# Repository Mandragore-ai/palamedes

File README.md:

# Alea Palamedis — dés connectés pour Mandragore

**[Mandragore.ai](https://mandragore.ai/) · [Maitresinh@500nuancesdegeek.fr](mailto:Maitresinh@500nuancesdegeek.fr)**

**Licences :** firmware hardware et logiciels sous **AGPL-3.0**, logo et documentation sous **CC BY-SA 4.0**. Citation et partage à l'identique obligatoires ; licence commerciale sur demande pour qui ne veut pas publier ses modifications. Détails : [LICENCES.md](LICENCES.md).

**Mandragore.ai · 23 novembre 2026 · prototype : conçu et simulé, pas encore fabriqué**

Selon la légende, Palamède a inventé les dés pendant le siège de Troie, puis les a consacrés à Tyché, déesse du hasard. *Alea Palamedis*, ce sont ses dés, avec du Bluetooth.

Chaque dé connaît la face sur laquelle il s'arrête et l'annonce par Bluetooth au **Mentor** (aide au MJ pendant la partie de jeu de rôle) et au **Sage en direct** (jeux de plateau). Le Mentor reçoit le jet comme un fait, sans devoir le deviner dans la parole, et le relie à l'action déclenchée et à la fiche du personnage. Le dé peut aussi signaler sa valeur à une tablette ou à un plateau à l'encre conductrice par des pastilles capacitives invisibles, cachées sous la peinture.

## Principe

- **Pas de circuit souple ni de moulage délicat** : un petit cœur rond (Ø16 mm) est noyé dans la résine, à l'intérieur d'une coque imprimée en deux parties qui sert de moule. Le dé final est plein et équilibré.
- **Électronique** : module Bluetooth Fanstel BC832 (nRF52832), accéléromètre LIS2DH12, pile bouton rechargeable LIR1254, recharge sans fil.
- **Recharge** : une boîte recharge les 7 dés d'un set. Une bobine gravée dans le circuit imprimé se trouve sous chaque logement ; chaque emplacement détecte le dé posé et s'arrête seul.
- **Premier dé : D20.** Le D4 est un D8 numéroté deux fois de 1 à 4. Les coques D6, D8, D10 et D12 restent à dessiner.

## Points forts

- Cout minimisé
- Consommation électrique minimisée (autonomie accrue)
- Taille réduite (similaire à des dés normaux)
- Coque interchangeable (perrmet de changer de type de dé avec le même coeur)
- Présence, localisation et identité du dé (et résultat) transmis à un écran capacitif

## Contenu du dépôt

| Dossier | Contenu | État |
|---|---|---|
| [`materiel/coeur`](materiel/coeur) | cœur du dé v0.3 : paquet de commande JLCPCB (Gerbers, nomenclature, placement), projet KiCad | contrôle de conception sans erreur |
| [`materiel/chargeur`](materiel/chargeur) | carte émettrice de la boîte v0.1 : paquet JLCPCB, projet KiCad | contrôle de conception sans erreur |
| [`coques`](coques) | coque D20 en deux parties (STL), patron A4 des pastilles, notice de montage | à imprimer |
| [`boite`](boite) | boîte-chargeur 7 dés (STL) et sa notice | à imprimer |
| [`firmware`](firmware) | firmware du dé (nRF52) et du chargeur (CH32V203), binaires, variante de carte | compilé, pas encore essayé sur le matériel |
| [`logiciel`](logiciel) | client Web Bluetooth (TypeScript), journal des jets pour le Mentor, module Tabletop Kit, note d'intégration Mandragore | types vérifiés |
| [`simulations`](simulations) | pastilles capacitives (BEM), recharge sans fil (SPICE, Monte-Carlo), résultats | voir ci-dessous |
| [`scripts`](scripts) | génération des circuits (KiCad / pcbnew), routeur, coques et boîte (trimesh) | — |

## Ce qui a été simulé

- **Pastilles capacitives** (simulation électrostatique) : avec 4 groupes de pastilles dispersés sur les faces, le signal garde 76 à 84 % de celui d'une pastille indépendante par face. Sur une tablette, il atteint environ 36 à 46 % du signal d'un doigt.
- **Recharge sans fil** : la tension reçue dans le dé reste entre 5,0 et 5,7 V pour un écart de 1,5 à 2,5 mm et un décentrage jusqu'à 1,5 mm, tolérances des composants comprises (Monte-Carlo). Pile pleine, le dé court-circuite sa bobine pour ne rien chauffer.

## À valider sur le premier prototype

1. Mesurer la tension de recharge reçue dans le dé et le seuil de détection du chargeur.
2. Faire une mise à jour Bluetooth complète **avant** de couler la résine.
3. Vérifier l'équité du dé : 500 lancers et un test du χ².

Vous poursuivez ce travail ? Envoyez-nous vos mesures et vos améliorations, ou ouvrez une issue / pull request.

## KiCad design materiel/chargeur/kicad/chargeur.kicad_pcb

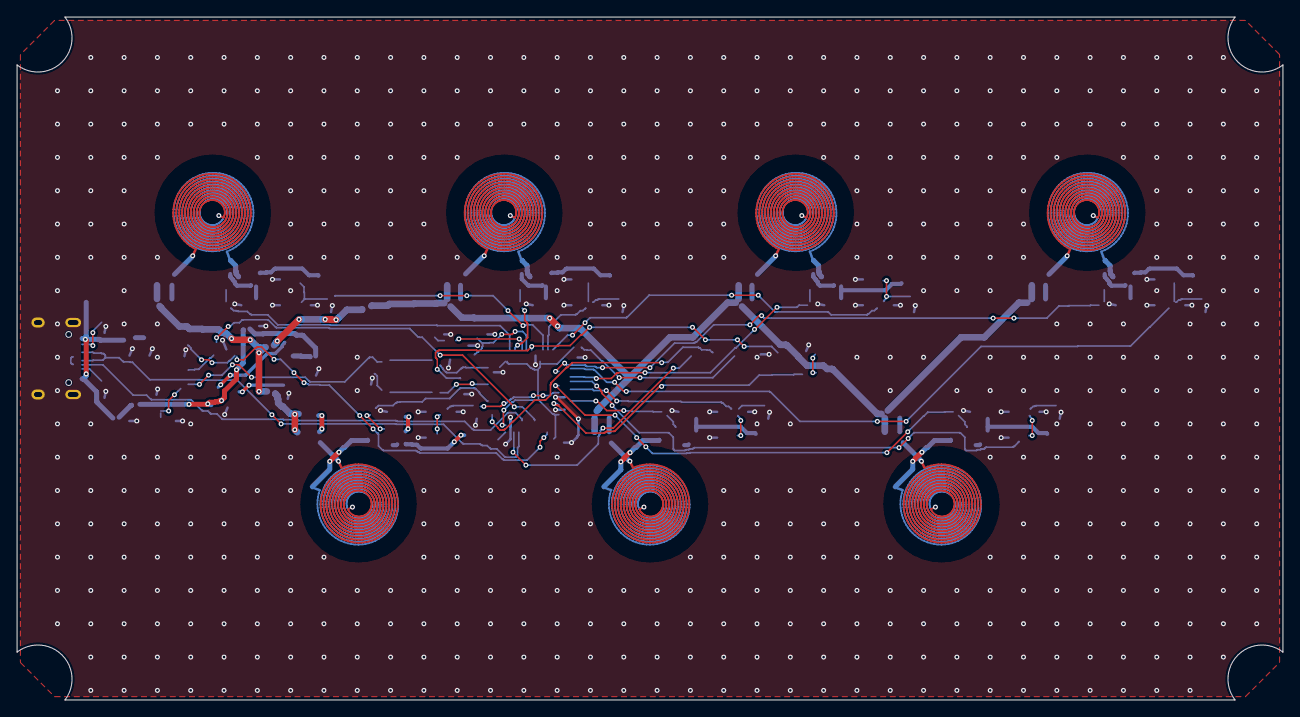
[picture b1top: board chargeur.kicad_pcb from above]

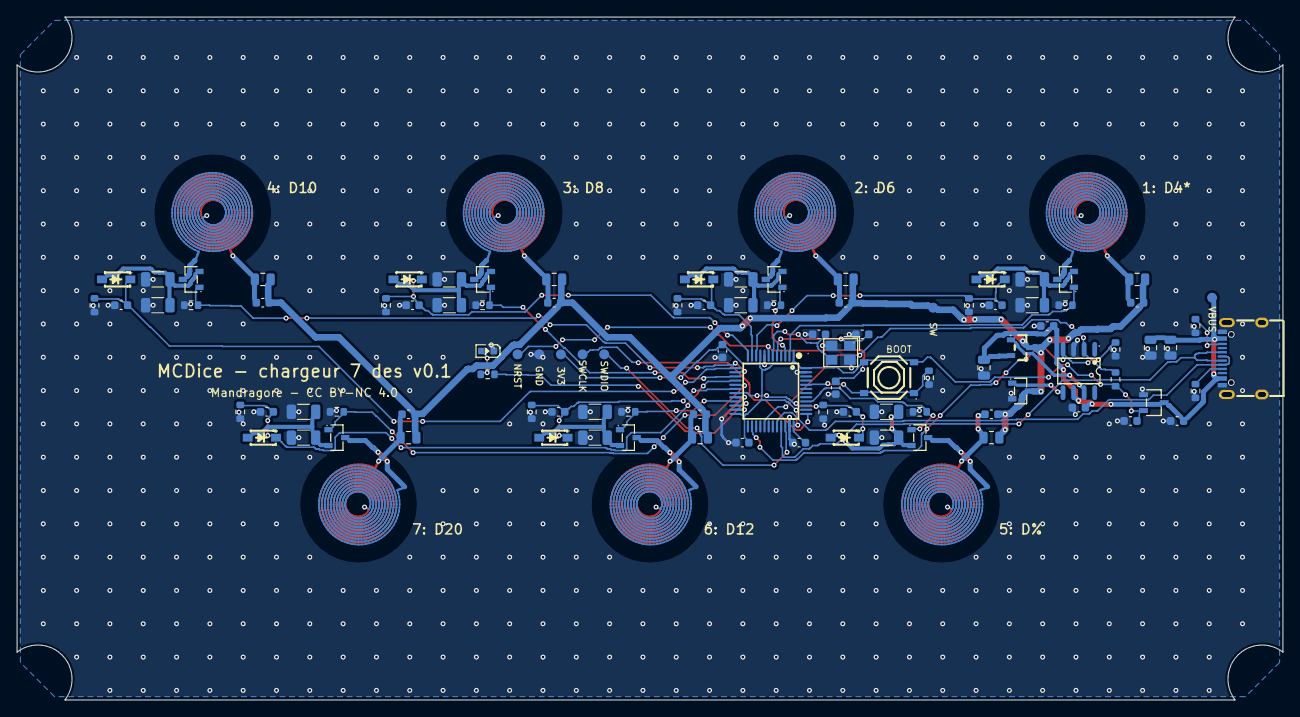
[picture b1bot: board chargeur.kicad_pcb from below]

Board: 2 copper layers, 152.0 x 82.0 mm, 98 parts (98 on the bottom side), 48 nets.

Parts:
C1, C2, C6: 22uF; C_0805_2012Metric
C3, C4, C5: 1uF; C_0603_1608Metric
C7, C10, C11, C12, C14, C41, C42, C43, C44, C45, C46, C47: 100nF; C_0603_1608Metric
C8, C9: 20pF; C_0603_1608Metric
C21, C22, C23, C24, C25, C26, C27: 10nF C0G; C_0805_2012Metric
C31, C32, C33, C34, C35, C36, C37: 2.2nF C0G; C_0603_1608Metric
D1: LED verte; LED0603-RD
D11, D12, D13, D14, D15, D16, D17: B5819W; SOD-123_L2.7-W1.6-LS3.7-RD-1
J1: USB-C 16P; USB-C-SMD_TYPE-C-16PIN-2MD-073
Q1: AO3401A; SOT-23_L2.9-W1.3-P1.90-LS2.4-BR
Q2, Q11, Q12, Q13, Q14, Q15, Q16, Q17: AO3400A; SOT-23-3_L2.9-W1.3-P1.90-LS2.4-BR
R1, R2: 5.1k; R_0603_1608Metric
R3, R4, R5: 10k; R_0603_1608Metric
R6: 1k; R_0603_1608Metric
R11, R12, R13, R14, R15, R16, R17, R41, R42, R43, R44, R45, R46, R47: 100k; R_0603_1608Metric
R21, R22, R23, R24, R25, R26, R27, R31, R32, R33, R34, R35, R36, R37: 2.2R; R_1206_3216Metric
SW1: BOOT; SW-SMD_4P-L5.1-W5.1-P3.70-LS6.5-TL_H1.5
TP1: SWDIO; TP_SWDIO
TP2: SWCLK; TP_SWCLK
TP3: 3V3; TP_3V3
TP4: GND; TP_GND
TP5: SW; TP_SW
TP6: VBUS; TP_VBUS
TP7: NRST; TP_NRST
U1: XC6206P332MR; SOT-23-3_L2.9-W1.6-P1.90-LS2.8-BR
U2: UCC27524ADR; SOIC-8_L4.9-W3.9-P1.27-LS6.0-BL
U3: CH32V203C8T6; LQFP-48_L7.0-W7.0-P0.50-LS9.0-BL
Y1: 8MHz; CRYSTAL-SMD_4P-L3.2-W2.5-BL

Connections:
3V3: C4.1, C10.1, C11.1, C12.1, R3.2, SW1.3, SW1.4, TP3.1, U1.2, U3.1, U3.9, U3.24, U3.36, U3.48
BOOT0: R5.1, SW1.1, SW1.2, U3.44
CC1: J1.A5, R1.1
CC2: J1.B5, R2.1
COIL1: C21.2, C31.2, Q11.3
COIL2: C22.2, C32.2, Q12.3
COIL3: C23.2, C33.2, Q13.3
COIL4: C24.2, C34.2, Q14.3
COIL5: C25.2, C35.2, Q15.3
COIL6: C26.2, C36.2, Q16.3
COIL7: C27.2, C37.2, Q17.3
EN1: Q11.1, R11.1, U3.2
EN2: Q12.1, R12.1, U3.3
EN3: Q13.1, R13.1, U3.15
EN4: Q14.1, R14.1, U3.14
EN5: Q15.1, R15.1, U3.40
EN6: Q16.1, R16.1, U3.21
EN7: Q17.1, R17.1, U3.17
GATE_H: Q1.1, U2.7
GATE_L: Q2.1, U2.5
GND: C1.2, C2.2, C3.2, C4.2, C5.2, C6.2, C7.2, C8.2, C9.2, C10.2, C11.2, C12.2, C14.2, C41.2, C42.2, C43.2, C44.2, C45.2, C46.2, C47.2, D1.1, J1.13, J1.14, J1.A1B12, J1.B1A12, Q2.2, R1.2, R2.2, R4.2, R5.2, R11.2, R12.2, R13.2, R14.2, R15.2, R16.2, R17.2, R21.2, R22.2, R23.2, R24.2, R25.2, R26.2, R27.2, R31.2, R32.2, R33.2, R34.2, R35.2, R36.2, R37.2, R41.2, R42.2, R43.2, R44.2, R45.2, R46.2, R47.2, TP4.1, U1.1, U2.3, U3.8, U3.20, U3.23, U3.35, U3.47, Y1.2, Y1.4
LED: R6.1, U3.22
LED_A: D1.2, R6.2
NRST: C14.1, TP7.1, U3.7
PK1: C41.1, D11.1, R41.1, U3.10
PK2: C42.1, D12.1, R42.1, U3.11
PK3: C43.1, D13.1, R43.1, U3.12
PK4: C44.1, D14.1, R44.1, U3.13
PK5: C45.1, D15.1, R45.1, U3.19
PK6: C46.1, D16.1, R46.1, U3.18
PK7: C47.1, D17.1, R47.1, U3.16
PWM_H: R3.1, U2.2, U3.29
PWM_L: R4.1, U2.4, U3.26
S1: D11.2, Q11.2, R21.1, R31.1
S2: D12.2, Q12.2, R22.1, R32.1
S3: D13.2, Q13.2, R23.1, R33.1
S4: D14.2, Q14.2, R24.1, R34.1
S5: D15.2, Q15.2, R25.1, R35.1
S6: D16.2, Q16.2, R26.1, R36.1
S7: D17.2, Q17.2, R27.1, R37.1
SW: C21.1, C22.1, C23.1, C24.1, C25.1, C26.1, C27.1, C31.1, C32.1, C33.1, C34.1, C35.1, C36.1, C37.1, Q1.3, Q2.3, TP5.1
SWCLK: TP2.1, U3.37
SWDIO: TP1.1, U3.34
USB_DM: J1.A7, J1.B7, U3.32
USB_DP: J1.A6, J1.B6, U3.33
VBUS: C1.1, C2.1, C3.1, C5.1, C6.1, C7.1, J1.A4B9, J1.B4A9, Q1.2, TP6.1, U1.3, U2.6
XIN: C8.1, U3.5, Y1.1
XOUT: C9.1, U3.6, Y1.3

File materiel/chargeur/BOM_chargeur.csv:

Comment,Designator,Footprint,LCSC Part #
22uF,"C1,C2,C6",C_0805_2012Metric,C45783
100nF,"C10,C11,C12,C14,C41,C42,C43,C44,C45,C46,C47,C7",C_0603_1608Metric,C14663
10nF C0G,"C21,C22,C23,C24,C25,C26,C27",C_0805_2012Metric,C27071
1uF,"C3,C4,C5",C_0603_1608Metric,C15849
2.2nF C0G,"C31,C32,C33,C34,C35,C36,C37",C_0603_1608Metric,C33353
20pF,"C8,C9",C_0603_1608Metric,C1648
LED verte,D1,LED0603-RD,C72043
B5819W,"D11,D12,D13,D14,D15,D16,D17",SOD-123_L2.7-W1.6-LS3.7-RD-1,C8598
USB-C 16P,J1,USB-C-SMD_TYPE-C-16PIN-2MD-073,C2765186
AO3401A,Q1,SOT-23_L2.9-W1.3-P1.90-LS2.4-BR,C15127
AO3400A,"Q11,Q12,Q13,Q14,Q15,Q16,Q17,Q2",SOT-23-3_L2.9-W1.3-P1.90-LS2.4-BR,C20917
5.1k,"R1,R2",R_0603_1608Metric,C23186
100k,"R11,R12,R13,R14,R15,R16,R17,R41,R42,R43,R44,R45,R46,R47",R_0603_1608Metric,C25803
2.2R,"R21,R22,R23,R24,R25,R26,R27,R31,R32,R33,R34,R35,R36,R37",R_1206_3216Metric,C17947
10k,"R3,R4,R5",R_0603_1608Metric,C25804
1k,R6,R_0603_1608Metric,C21190
BOOT,SW1,SW-SMD_4P-L5.1-W5.1-P3.70-LS6.5-TL_H1.5,C318884
XC6206P332MR,U1,SOT-23-3_L2.9-W1.6-P1.90-LS2.8-BR,C5446
UCC27524ADR,U2,SOIC-8_L4.9-W3.9-P1.27-LS6.0-BL,C185857
CH32V203C8T6,U3,LQFP-48_L7.0-W7.0-P0.50-LS9.0-BL,C3001172
8MHz,Y1,CRYSTAL-SMD_4P-L3.2-W2.5-BL,C2682774

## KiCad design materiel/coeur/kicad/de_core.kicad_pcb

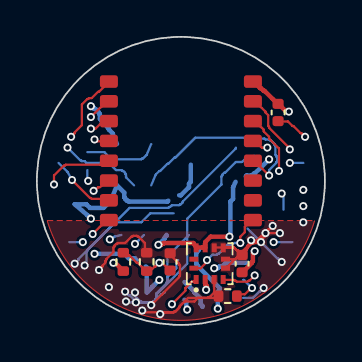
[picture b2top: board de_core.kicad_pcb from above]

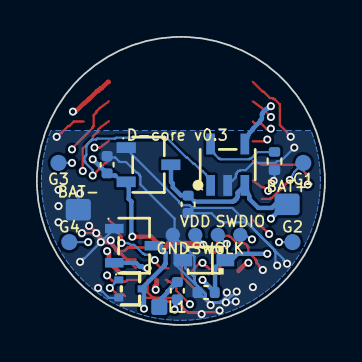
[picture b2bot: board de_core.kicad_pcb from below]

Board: 4 copper layers, 16.0 x 16.0 mm, 29 parts (21 on the bottom side), 19 nets.

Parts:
C1, C2, C9: 100nF; C_0402_1005Metric
C5: 1nF C0G; C_0402_1005Metric
C6, C7, C8: 4.7uF; C_0402_1005Metric
D2: BAT54S; SOT-23-3_L3.0-W1.7-P0.95-LS2.9-BR
Q1: 2N7002T; SOT-523-3_L1.6-W0.8-P0.50-LS1.6-BR
R1: 33k; R_0402_1005Metric
R2, R3: 1M; R_0402_1005Metric
R4: 100k; R_0402_1005Metric
TP_BATN: BAT-; pad_BAT-
TP_BATP: BAT+; pad_BAT+
TP_G1: G1; pad_G1
TP_G2: G2; pad_G2
TP_G3: G3; pad_G3
TP_G4: G4; pad_G4
TP_GND: GND; pad_GND
TP_L1: COIL1; pad_COIL1
TP_SWCLK: SWCLK; pad_SWCLK
TP_SWDIO: SWDIO; pad_SWDIO
TP_VDD: VDD; pad_VDD
U1: BC832 (nRF52832); Fanstel_BC832
U2: LIS2DH12TR; LGA-12_L2.0-W2.0-P0.50-BL
U3: TP4054; SOT-23-5_L3.0-W1.7-P0.95-LS2.8-BL
U4: XC6206P302MR; SOT-23-3_L2.9-W1.6-P1.90-LS2.8-BR
Z1: BZT52C5V6S; SOD-323_L1.8-W1.3-LS2.5-RD

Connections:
ACC_INT: U1.9, U2.12
CAP_G1: TP_G1.1, U1.7
CAP_G2: TP_G2.1, U1.8
CAP_G3: TP_G3.1, U1.6
CAP_G4: TP_G4.1, U1.5
CHRG: U1.12, U3.1
COIL1: C5.1, TP_L1.1
GND: C1.2, C2.2, C6.2, C7.2, C8.2, C9.2, D2.1, Q1.2, R1.2, R3.2, R4.2, TP_BATN.1, TP_GND.1, U1.1, U2.3, U2.5, U2.6, U2.7, U2.8, U3.2, U4.1, Z1.2
PROG: R1.1, U3.5
RX_SHORT: Q1.1, R4.1, U1.2
RX_X: C5.2, D2.3, Q1.3
SCL: U1.14, U2.1
SDA: U1.15, U2.4
SWCLK: TP_SWCLK.1, U1.4
SWDIO: TP_SWDIO.1, U1.3
VBAT: C7.1, R2.1, TP_BATP.1, U3.3, U4.3
VBAT_SENSE: C9.1, R2.2, R3.1, U1.13
VDD: C1.1, C2.1, C8.1, TP_VDD.1, U1.16, U2.2, U2.9, U2.10, U4.2
VRECT: C6.1, D2.2, U3.4, Z1.1

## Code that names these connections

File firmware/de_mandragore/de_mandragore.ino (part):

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// ---------------------------------------------------------------- broches (P0.xx = numéro Arduino sur nRF52832)
#define PIN_SDA      26
#define PIN_SCL      27
#define PIN_ACC_INT  3
#define PIN_PILE     2    // AIN0 : pont 1 MΩ / 1 MΩ -> VBAT/2
#define PIN_CHRG     1    // TP4054 : bas = en charge
#define PIN_RX_SHORT 20   // Q1 (2N7002T) : haut = bobine court-circuitée (pile pleine sur le chargeur)
#define VBAT_PLEINE  4.15f  // au-dessus : on court-circuite la bobine (la zener ne chauffe plus)
#define VBAT_REPRISE 4.00f  // en dessous : on relâche, la charge reprend

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void gererCourtCircuit(float v) {
  if (!bobineCourtCircuitee && v >= VBAT_PLEINE) bobineCourtCircuitee = true;
  else if (bobineCourtCircuitee && v <= VBAT_REPRISE) bobineCourtCircuitee = false;
  digitalWrite(PIN_RX_SHORT, bobineCourtCircuitee ? HIGH : LOW);
}
uint8_t niveauPile() {
  float v = tensionPile();
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
// ---------------------------------------------------------------- démarrage
void setup() {
  pinMode(PIN_RX_SHORT, OUTPUT); digitalWrite(PIN_RX_SHORT, LOW);   // R4 100 kΩ tient la grille à la masse au repos
  pinMode(PIN_CHRG, INPUT_PULLUP);
  pinMode(PIN_ACC_INT, INPUT);
  groupesHauteImpedance();
  InternalFS.begin(); charger();
  Wire.setPins(PIN_SDA, PIN_SCL); Wire.begin(); Wire.setClock(400000);
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  if (poseDemandee && calme > 25) { float an[3] = {a[0]/n, a[1]/n, a[2]/n}; etalonner(poseDemandee, an); poseDemandee = 0; }


  if (millis() - dernierMouvement > VEILLE_MS && !Bluefruit.connected() && digitalRead(PIN_CHRG) == HIGH) {
    ledEteinte(); groupesHauteImpedance(); accLire(0x31);       // réarme l'interruption de mouvement
    systemOff(PIN_ACC_INT, HIGH);                                // réveil au prochain mouvement (redémarrage)
  }
  delay(20);
}
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

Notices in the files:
materiel/chargeur/kicad/chargeur.kicad_pcb:
Mandragore - CC BY-NC 4.0
